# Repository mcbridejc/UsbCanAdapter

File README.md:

# USB CAN Adapter

An STM32F0 USB CAN interface. I couldn't find a decent option in stock, so built this. It works,
but is not well documented and should be considered a project not a product ;).

## Firmware

This board can use the "cantact" firmware from https://github.com/candle-usb/candleLight_fw. In the
release archive, the file is "cantact_fw.bin". It is also included in the repo here for reference.

It can be programmed via the built-in DFU bootloader. To get into boot loader, pull boot0 high while
powering on, using the BOOT0 button (See rev1 errata; some bodge wires are required for this).

On linux, you can use `dfu-util`, like so:

```
dfu-util -D cantact_fw.bin -d 0483:df11 -a 0 -s 0x08000000
```

ST has a DFU programming tool for windows (and there are others)

## Jumpers

There are three shortable jumpers:

- "TERM" connects a 120 ohm termination resistor between CAN_H and CAN_L.
- "POWER_ISO" (two jumpers) connect the USB 5V and ground to the isolated CAN bus side of the
  transceiver. If these are left unconnected, the CAN bus is electrically isolated from the MCU/USB
  side of the board, but 5V must be provided from elsewhere.

## Reminders for using on linux

`sudo ip link set can0 type can bitrate 1000000`
`sudo ip link set up can0 txqueuelen 1024`

For a GUI, SavvyCAN works. Create the connection as a "QT SerialBus" device, with devicetype "socketcan". It seems the link must be manually brought up and bitrate set on the command line first; savvy can isn't going it (maybe because of permissions?).

## Rev 1 Errata

- The BOOT0 button is backwards. It should be grounded by default and pulled high by the button.
- The jumper holes are too small for most 0.1" headers and need to be enlarged.

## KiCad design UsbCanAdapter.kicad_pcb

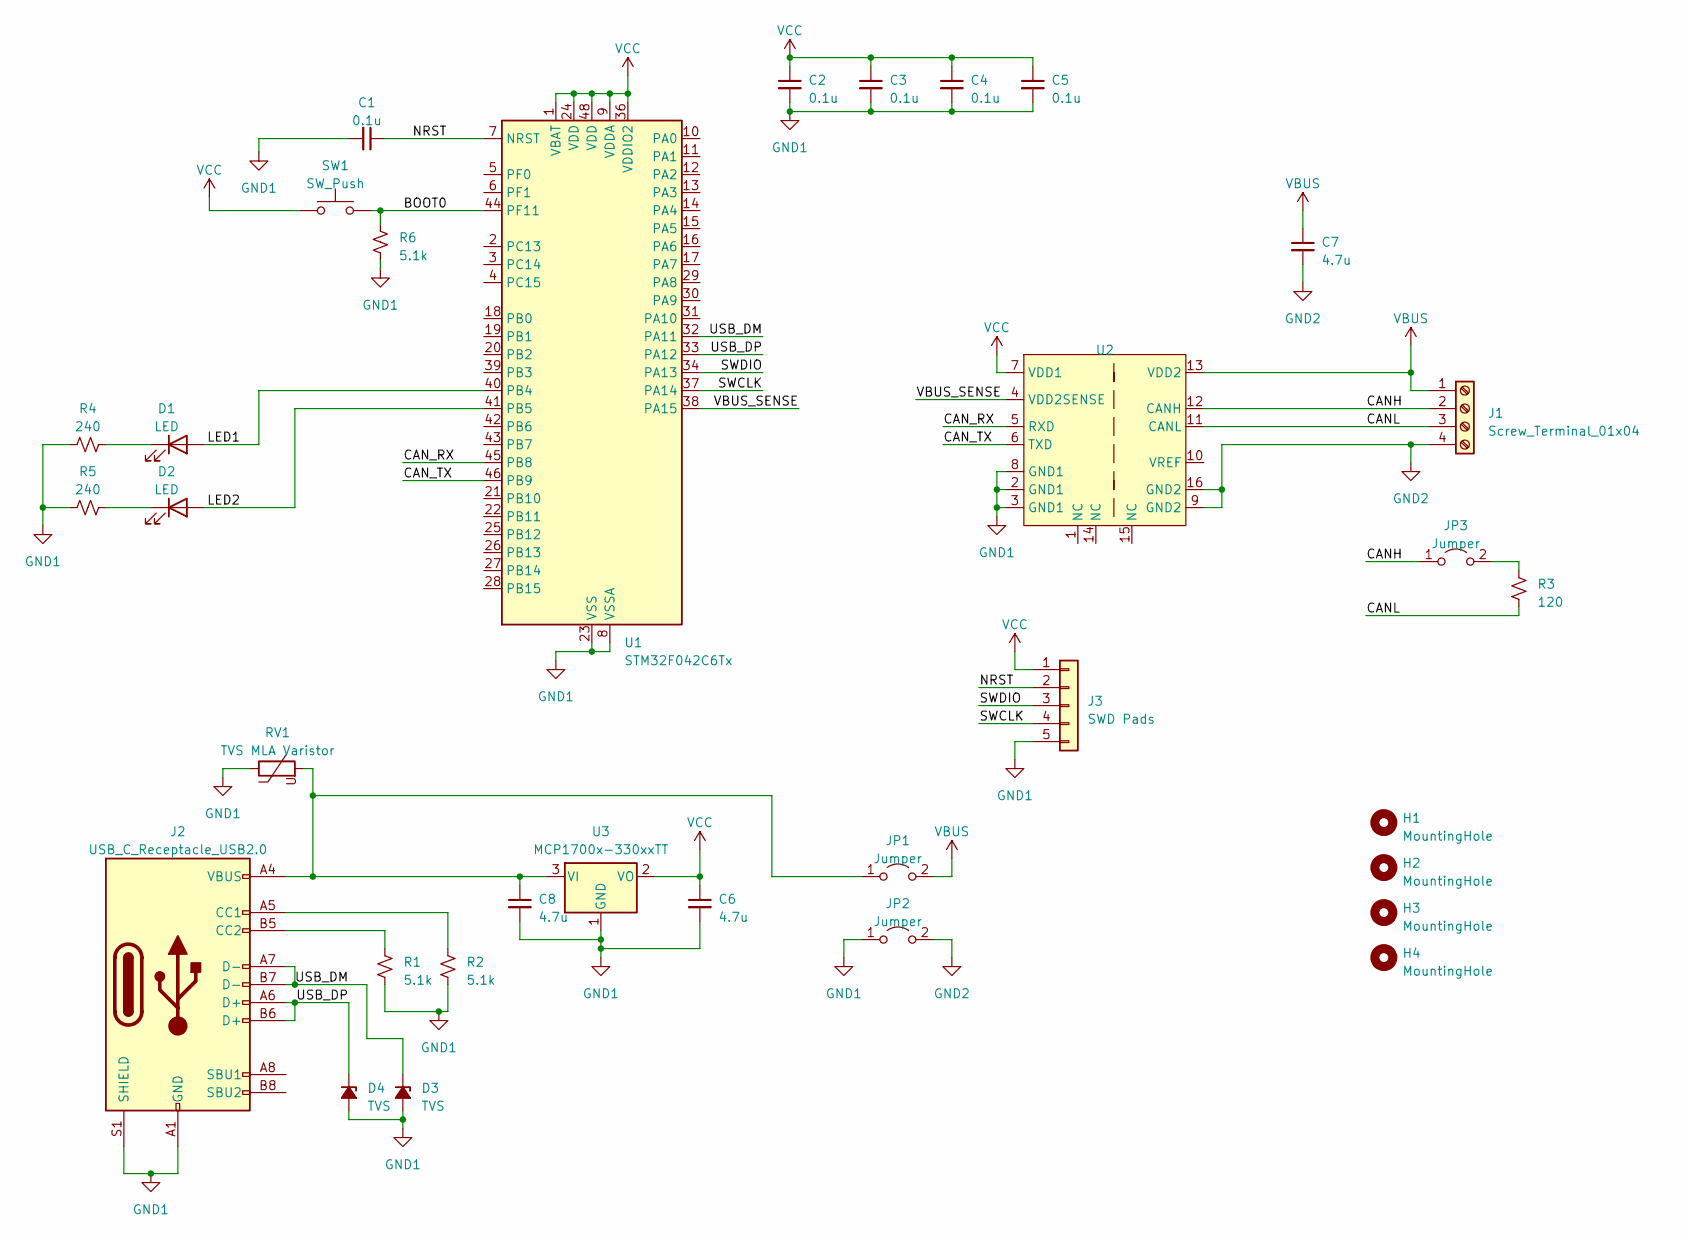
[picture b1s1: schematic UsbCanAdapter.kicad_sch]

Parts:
C1, C2, C3, C4, C5: 0.1u; C_0603_1608Metric
C6, C7, C8: 4.7u; C_0805_2012Metric
D1, D2: LED; LED_0805_2012Metric
D3, D4: TVS; D_0402_1005Metric_Pad0.77x0.64mm_HandSolder
H1, H2, H3, H4: MountingHole; MountingHole_2.2mm_M2
J1: Screw_Terminal_01x04; 1776119-4; Mfg Part Number 1776119-4
J2: USB_C_Receptacle_USB2.0; USB_C_Receptacle_GCT_USB4105-xx-A_16P_TopMnt_Horizontal
J3: SWD Pads; SWD_PADS
JP1, JP2, JP3: Jumper; short_jumper
R1, R2, R6: 5.1k; R_0603_1608Metric
R3: 120; R_0603_1608Metric
R4, R5: 240; R_0603_1608Metric
RV1: TVS MLA Varistor; R_0603_1608Metric
SW1: SW_Push; SW_SPST_PTS810; Mfg Part Number PTS810 SJM 250 SMTR LFS
U1: STM32F042C6Tx; LQFP-48_7x7mm_P0.5mm
U2: SOIC-16W_7.5x10.3mm_P1.27mm; Mfg Part Number ADM3054WBRWZ-RL7
U3: MCP1700x-330xxTT; SOT-23

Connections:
/BOOT0: R6.1, SW1.2, U1.44 (PF11)
/CANH: J1.2, JP3.1 (A), U2.12 (CANH)
/CANL: J1.3, R3.1, U2.11 (CANL)
/CAN_RX: U1.45 (PB8), U2.5 (RXD)
/CAN_TX: U1.46 (PB9), U2.6 (TXD)
/LED1: D1.2 (A), U1.40 (PB4)
/LED2: D2.2 (A), U1.41 (PB5)
/NRST: C1.1, J3.2, U1.7 (NRST)
/SWCLK: J3.4, U1.37 (PA14)
/SWDIO: J3.3, U1.34 (PA13)
/USB_DM: D3.1 (K), J2.A7 (D-), J2.B7 (D-), U1.32 (PA11)
/USB_DP: D4.1 (K), J2.A6 (D+), J2.B6 (D+), U1.33 (PA12)
/VBUS_SENSE: U1.38 (PA15), U2.4 (VDD2SENSE)
GND1: C1.2, C2.2, C3.2, C4.2, C5.2, C6.2, C8.2, D3.2 (A), D4.2 (A), J2.A1 (GND), J2.A12 (GND), J2.B1 (GND), J2.B12 (GND), J2.S1 (SHIELD), J3.5, JP2.1 (A), R1.2, R2.2, R4.1, R5.1, R6.2, RV1.1, U1.8 (VSSA), U1.23 (VSS), U1.35 (VSS), U1.47 (VSS), U2.2 (GND1), U2.3 (GND1), U2.8 (GND1), U3.1 (GND)
GND2: C7.2, J1.4, JP2.2 (B), U2.9 (GND2), U2.16 (GND2)
unnamed: D1.1 (K), R4.2
unnamed: D2.1 (K), R5.2
unnamed: J2.A5 (CC1), R2.1
unnamed: J2.B5 (CC2), R1.1
unnamed: C8.1, J2.A4 (VBUS), J2.A9 (VBUS), J2.B4 (VBUS), J2.B9 (VBUS), JP1.1 (A), RV1.2, U3.3 (VI)
unnamed: JP3.2 (B), R3.2
VBUS: C7.1, J1.1, JP1.2 (B), U2.13 (VDD2)
VCC: C2.1, C3.1, C4.1, C5.1, C6.1, J3.1, SW1.1, U1.1 (VBAT), U1.9 (VDDA), U1.24 (VDD), U1.36 (VDDIO2), U1.48 (VDD), U2.7 (VDD1), U3.2 (VO)

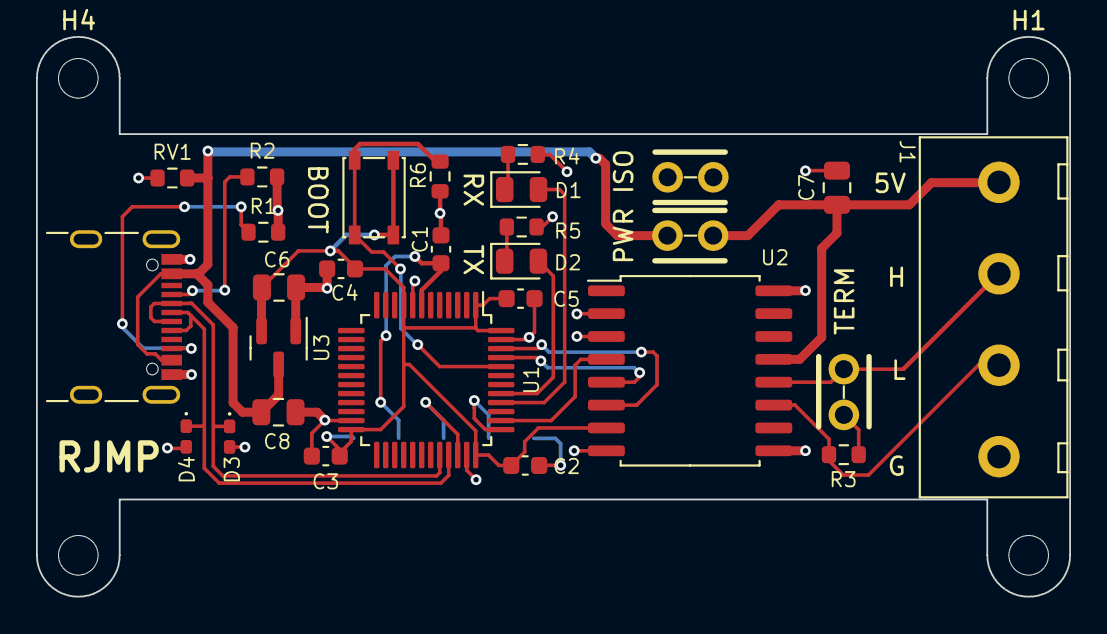
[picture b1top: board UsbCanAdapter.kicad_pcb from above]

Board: 2 copper layers, 57.4 x 31.1 mm, 33 parts (1 on the bottom side), 23 nets.

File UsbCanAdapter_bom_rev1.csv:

Component,Description,Part,References,Value,Footprint,Quantity Per PCB,Datasheet,Mfg Part Number,DK Part Number
1,"Unpolarized capacitor, small symbol",C_Small,C1 C2 C3 C4 C5,0.1u,C_0603_1608Metric,5,~,,
2,"Unpolarized capacitor, small symbol",C_Small,C6 C7 C8,4.7u,C_0805_2012Metric,3,~,,
3,Light emitting diode,LED,D1 D2,LED,LED_0805_2012Metric,2,~,,
4,"Zener diode, small symbol, filled shape",D_Zener_Small_Filled,D3 D4,TVS,D_0402_1005Metric_Pad0.77x0.64mm_HandSolder,2,~,,
5,"Generic connector, single row, 01x05, script generated (kicad-library-utils/schlib/autogen/connector/)",Conn_01x05,J3,SWD Pads,SWD_PADS,1,~,,
6,"Generic screw terminal, single row, 01x04, script generated (kicad-library-utils/schlib/autogen/connector/)",Screw_Terminal_01x04,J1,Screw_Terminal_01x04,1776119-4,1,~,1776119-4,
7,USB 2.0-only Type-C Receptacle connector,USB_C_Receptacle_USB2.0,J2,USB_C_Receptacle_USB2.0,USB_C_Receptacle_GCT_USB4105-xx-A_16P_TopMnt_Horizontal,1,https://www.usb.org/sites/default/files/documents/usb_type-c.zip,,
8,"Jumper, 2-pole, open",Jumper_2_Open,JP1 JP2 JP3,Jumper,short_jumper,3,~,,
9,"Resistor, small US symbol",R_Small_US,R3,120,R_0603_1608Metric,1,~,,
10,"Resistor, small US symbol",R_Small_US,R4 R5,240,R_0603_1608Metric,2,~,,
11,"Resistor, small US symbol",R_Small_US,R1 R2,5.1k,R_0603_1608Metric,2,~,,
12,Voltage dependent resistor,Varistor,RV1,TVS MLA Varistor,R_0603_1608Metric,1,~,,
13,"Push button switch, generic, two pins",SW_Push,SW1,SW_Push,SW_SPST_PTS810,1,~,PTS810 SJM 250 SMTR LFS,CKN10502CT-ND
14,"250mA Low Quiscent Current LDO, 3.3V output, SOT-23",MCP1700x-330xxTT,U3,MCP1700x-330xxTT,SOT-23,1,http://ww1.microchip.com/downloads/en/DeviceDoc/20001826D.pdf,,
15,"STMicroelectronics Arm Cortex-M0 MCU, 32KB flash, 6KB RAM, 48 MHz, 2.0-3.6V, 38 GPIO, LQFP48",STM32F042C6Tx,U1,STM32F042C6Tx,LQFP-48_7x7mm_P0.5mm,1,https://www.st.com/resource/en/datasheet/stm32f042c6.pdf,,
16,,ADB3054,U2,~,SOIC-16W_7.5x10.3mm_P1.27mm,1,,ADM3054WBRWZ-RL7,





Component Groups:,16
Component Count:,28
Fitted Components:,28
Number of PCBs:,1
Total components:,28
Schematic Version:,
Schematic Date:,
PCB Variant:,default
BoM Date:,Sat 18 Mar 2023 11:25:42 AM PDT
Schematic Source:,UsbCanAdapter.kicad_sch
KiCad Version:,Eeschema 7.0.0-da2b9df05c~171~ubuntu22.04.1

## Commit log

2024-04-30 initial commit of rev1 design
2024-04-30 rev1 gerbers
2024-04-30 Add a README
2024-04-30 Fix rev1 issues
    - reverse BOOT0 pin polarity
    - enlarge short jumper holes to 1mm
2024-04-30 Add 3D render to readme
2024-04-30 Remove fp-info-cache
2024-05-02 Update PCB design for rev2 changes
2024-05-02 Add firmware image
2024-05-02 Update readme about firmware programming
2024-05-02 Some setup instructions
2024-05-02 Add note about jumpers to readme
